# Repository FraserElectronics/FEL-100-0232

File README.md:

# FEL-100-0232
Z80 SoftROM Module PCB

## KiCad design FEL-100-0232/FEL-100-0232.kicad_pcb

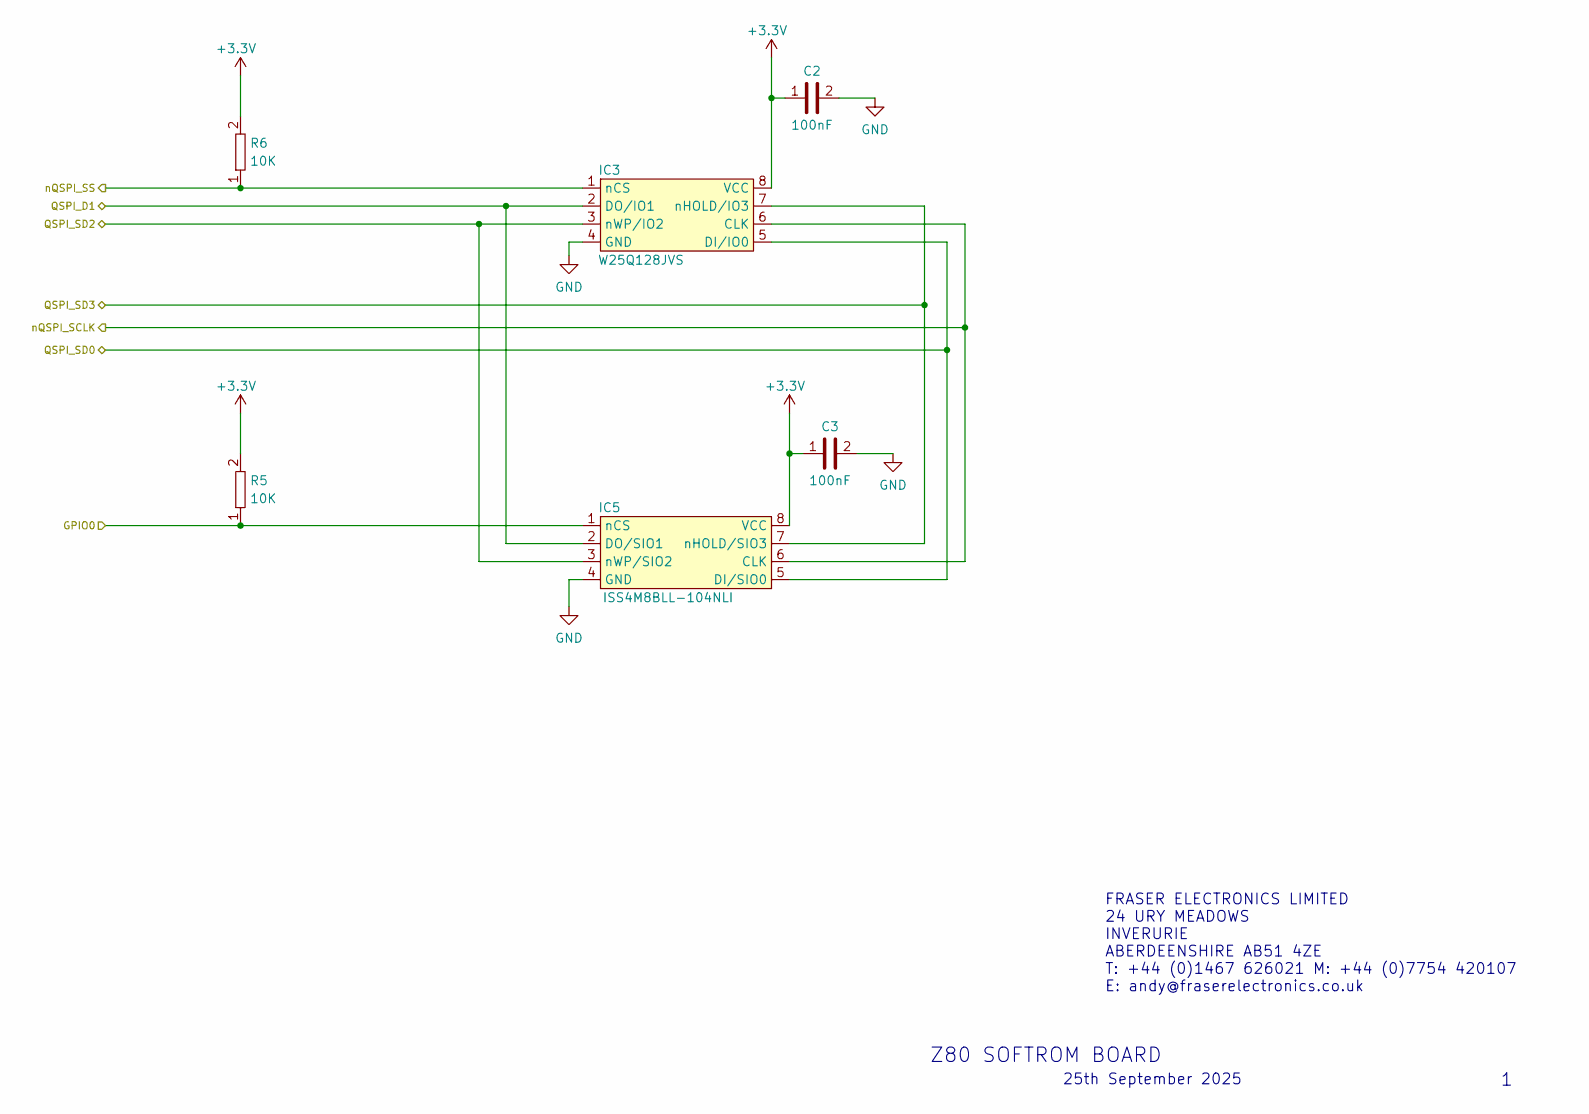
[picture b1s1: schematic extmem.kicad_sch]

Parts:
C2, C3: 100nF; C_0603_1608Metric; PartNumber FEL-002-0011
IC3: W25Q128JVS; SOIC-8_5.3x6.2mm_P1.27mm; PartNumber FEL-016-0290
IC5: ISS4M8BLL-104NLI; SOIC-8_5.3x6.2mm_P1.27mm; PartNumber FEL-016-0355
R5, R6: 10K; R_0603_1608Metric; PartNumber FEL-028-0028

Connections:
+3.3V: C2.1, C3.1, IC3.8 (VCC), IC5.8 (VCC), R5.2, R6.2; also elsewhere on the board
/External Memory/GPIO0: IC5.1 (nCS), R5.1; also elsewhere on the board
/External Memory/QSPI_D1: IC3.2 (DO/IO1), IC5.2 (DO/SIO1); also elsewhere on the board
/External Memory/QSPI_SD0: IC3.5 (DI/IO0), IC5.5 (DI/SIO0); also elsewhere on the board
/External Memory/QSPI_SD2: IC3.3 (nWP/IO2), IC5.3 (nWP/SIO2); also elsewhere on the board
/External Memory/QSPI_SD3: IC3.7 (nHOLD/IO3), IC5.7 (nHOLD/SIO3); also elsewhere on the board
/External Memory/nQSPI_SCLK: IC3.6 (CLK), IC5.6 (CLK); also elsewhere on the board
/RP2350B Micro/nQSPI_SS: IC3.1 (nCS), R6.1; also elsewhere on the board
GND: C2.2, C3.2, IC3.4 (GND), IC5.4 (GND); also elsewhere on the board

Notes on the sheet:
Z80 SOFTROM BOARD
FRASER ELECTRONICS LIMITED 24 URY MEADOWS INVERURIE ABERDEENSHIRE AB51 4ZE T: +44 (0)1467 626021 M: +44 (0)7754 420107 E: andy@fraserelectronics.co.uk
25th September 2025

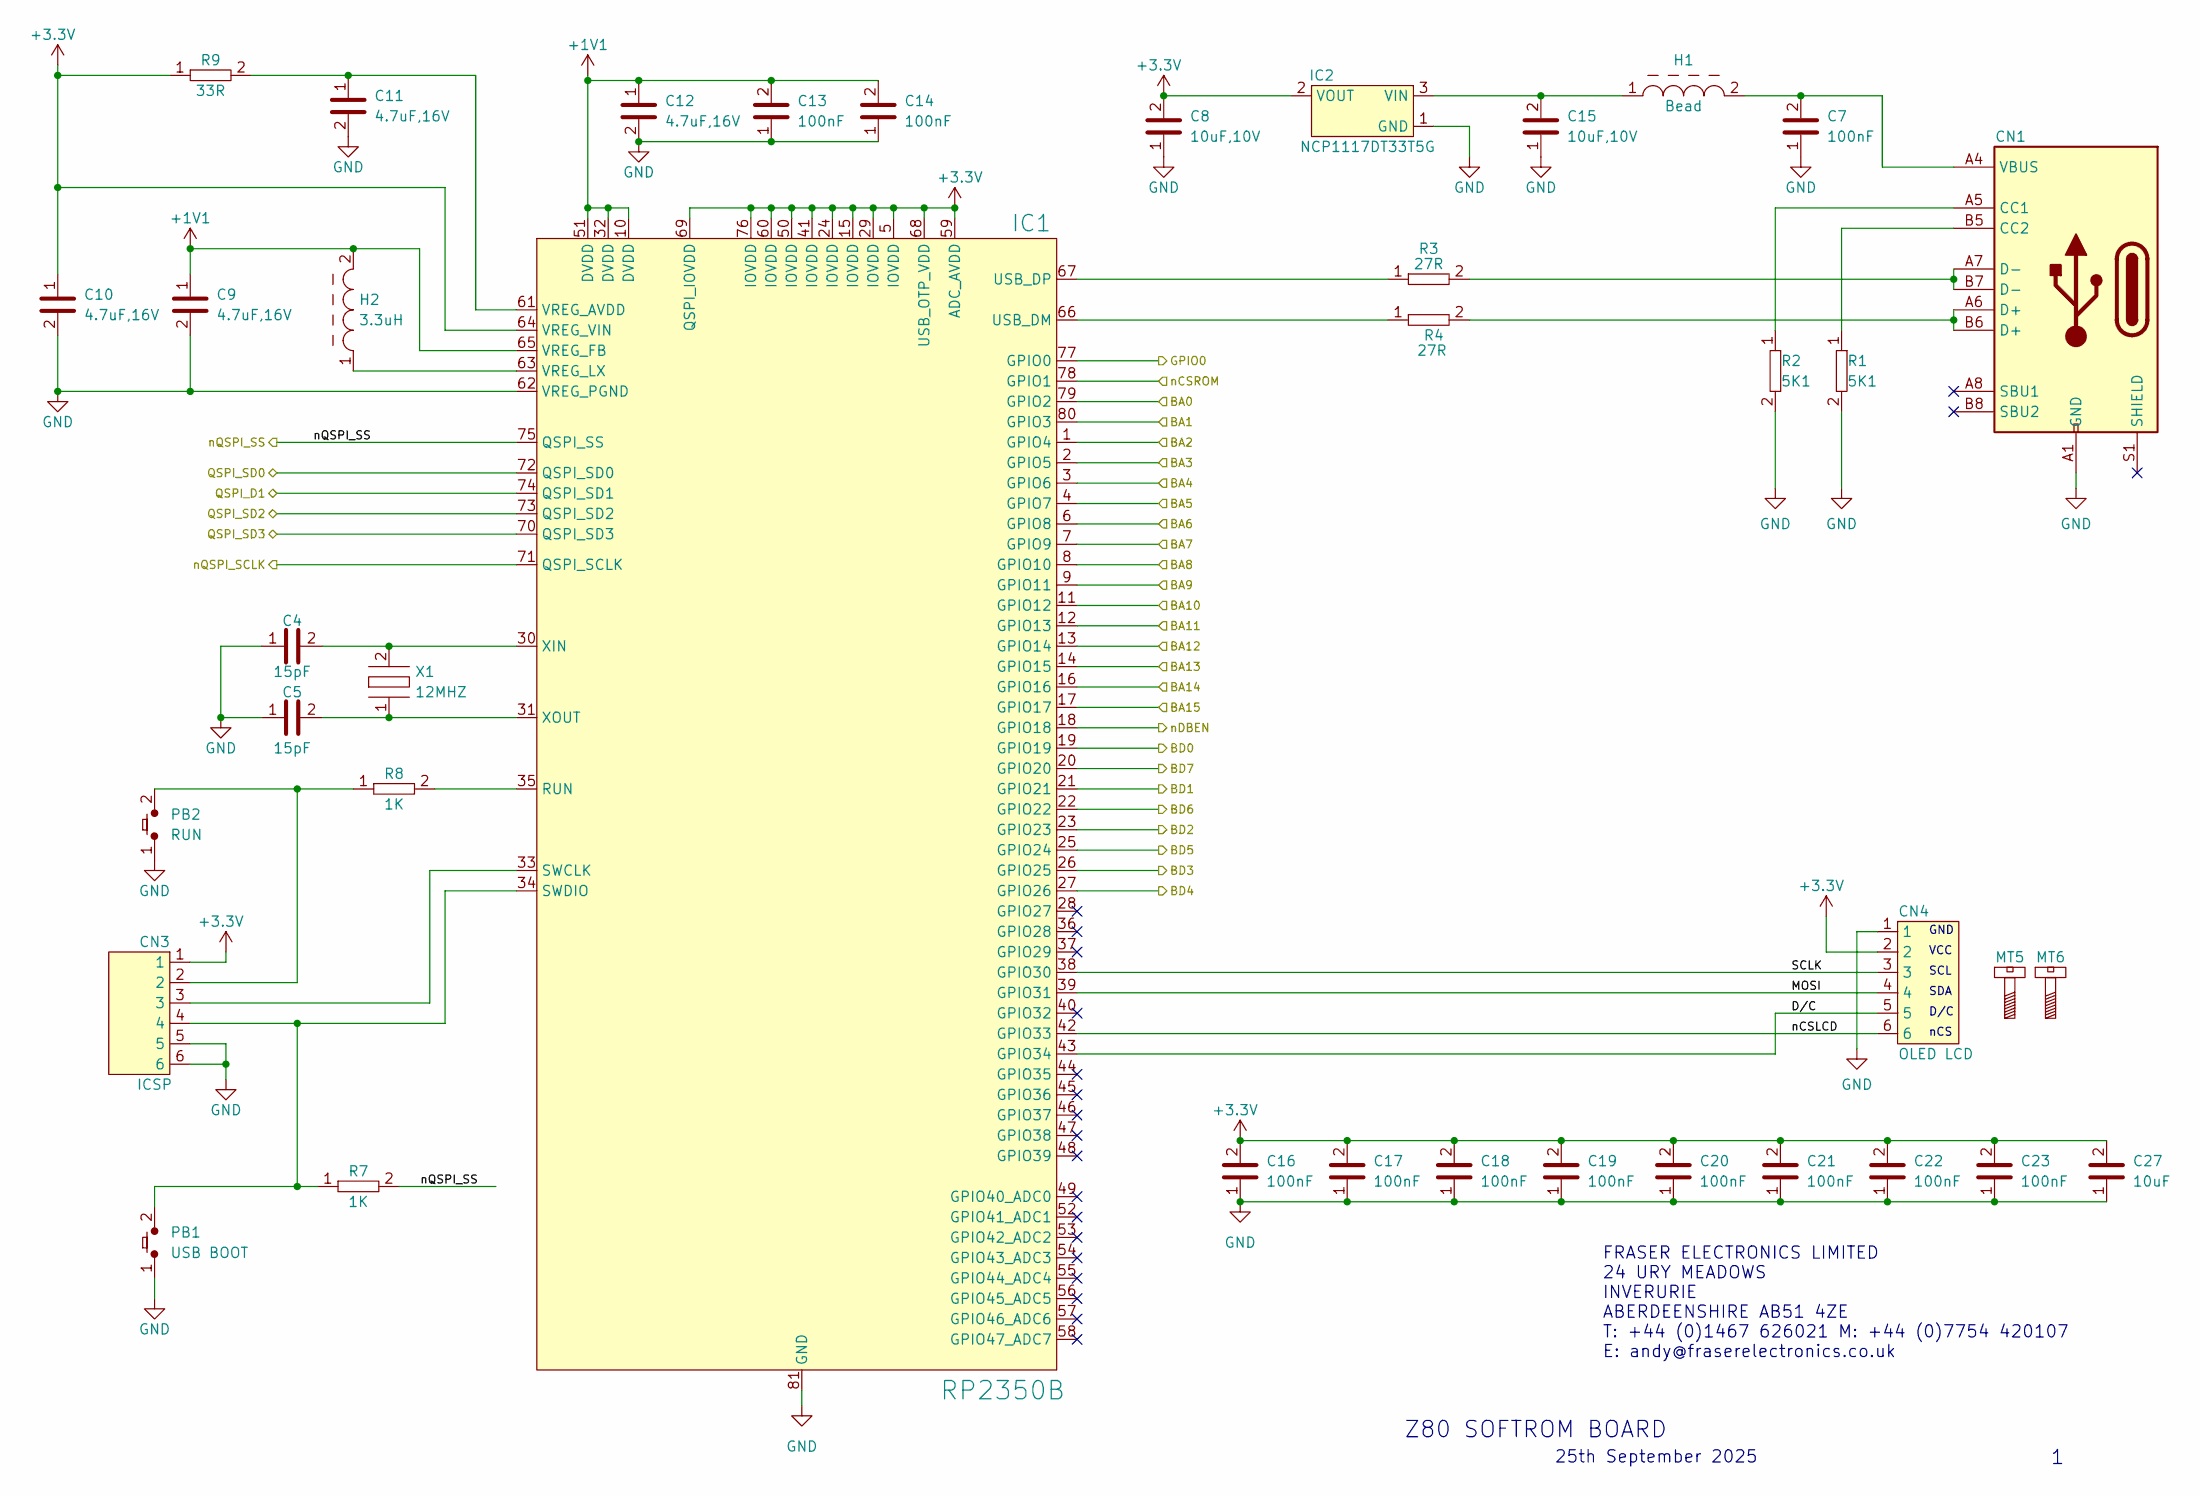
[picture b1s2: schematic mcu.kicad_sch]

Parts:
C4, C5: 15pF; C_0603_1608Metric; PartNumber FEL-002-0070
C7, C13, C14, C16, C17, C18, C19, C20, C21, C22, C23: 100nF; C_0603_1608Metric; PartNumber FEL-002-0011
C8, C15: 10uF,10V; C_0805_2012Metric; PartNumber FEL-002-0037
C9, C10, C11, C12: 4.7uF,16V; C_0805_2012Metric; PartNumber FEL-002-0013
C27: 10uF; C_0805_2012Metric; PartNumber FEL-002-0037
CN1: USB4105-GF-A-120; PartNumber FEL-004-0207
CN3: ICSP; M40-4010646R; PartNumber FEL-004-0006
CN4: OLED LCD; SIL6
H1: Bead; L_0603_1608Metric; PartNumber FEL-018-0016
H2: 3.3uH; AOTA-B201610S3R3-101-T; PartNumber FEL-018-0038
IC1: RP2350B; RP2350B_QFN-80_EP_10.573x10.573_Pitch0.4mm; PartNumber FEL-016-0353
IC2: NCP1117DT33T5G; TO-252-2; PartNumber FEL-016-0354
MT5, MT6: M3MountingHole
PB1: USB BOOT; EVQ-PT5A15; PartNumber FEL-030-0025
PB2: RUN; EVQ-PT5A15; PartNumber FEL-030-0025
R1, R2: 5K1; R_0603_1608Metric; PartNumber FEL-028-0083
R3, R4: 27R; R_0603_1608Metric; PartNumber FEL-028-0071
R7, R8: 1K; R_0603_1608Metric; PartNumber FEL-028-0037
R9: 33R; R_0603_1608Metric; PartNumber FEL-028-0045
X1: 12MHZ; ABM8-272-T3; PartNumber FEL-006-0008

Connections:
+1V1: C9.1, C12.1, C13.2, C14.2, H2.2, IC1.10 (DVDD), IC1.32 (DVDD), IC1.51 (DVDD), IC1.65 (VREG_FB)
+3.3V: C8.2, C10.1, C16.2, C17.2, C18.2, C19.2, C20.2, C21.2, C22.2, C23.2, C27.2, CN3.1, CN4.2, IC1.5 (IOVDD), IC1.15 (IOVDD), IC1.24 (IOVDD), IC1.29 (IOVDD), IC1.41 (IOVDD), IC1.50 (IOVDD), IC1.59 (ADC_AVDD), IC1.60 (IOVDD), IC1.64 (VREG_VIN), IC1.68 (USB_OTP_VDD), IC1.69 (QSPI_IOVDD), IC1.76 (IOVDD), IC2.2 (VOUT), R9.1; also elsewhere on the board
/External Memory/GPIO0: IC1.77 (GPIO0); also elsewhere on the board
/External Memory/QSPI_D1: IC1.74 (QSPI_SD1); also elsewhere on the board
/External Memory/QSPI_SD0: IC1.72 (QSPI_SD0); also elsewhere on the board
/External Memory/QSPI_SD2: IC1.73 (QSPI_SD2); also elsewhere on the board
/External Memory/QSPI_SD3: IC1.70 (QSPI_SD3); also elsewhere on the board
/External Memory/nQSPI_SCLK: IC1.71 (QSPI_SCLK); also elsewhere on the board
/RP2350B Micro/BA0: IC1.79 (GPIO2); also elsewhere on the board
/RP2350B Micro/BA1: IC1.80 (GPIO3); also elsewhere on the board
/RP2350B Micro/BA2: IC1.1 (GPIO4); also elsewhere on the board
/RP2350B Micro/BA3: IC1.2 (GPIO5); also elsewhere on the board
/RP2350B Micro/BA4: IC1.3 (GPIO6); also elsewhere on the board
/RP2350B Micro/BA5: IC1.4 (GPIO7); also elsewhere on the board
/RP2350B Micro/BA6: IC1.6 (GPIO8); also elsewhere on the board
/RP2350B Micro/BA7: IC1.7 (GPIO9); also elsewhere on the board
/RP2350B Micro/BA8: IC1.8 (GPIO10); also elsewhere on the board
/RP2350B Micro/BA9: IC1.9 (GPIO11); also elsewhere on the board
/RP2350B Micro/BA10: IC1.11 (GPIO12); also elsewhere on the board
/RP2350B Micro/BA11: IC1.12 (GPIO13); also elsewhere on the board
/RP2350B Micro/BA12: IC1.13 (GPIO14); also elsewhere on the board
/RP2350B Micro/BA13: IC1.14 (GPIO15); also elsewhere on the board
/RP2350B Micro/BA14: IC1.16 (GPIO16); also elsewhere on the board
/RP2350B Micro/BA15: IC1.17 (GPIO17); also elsewhere on the board
/RP2350B Micro/BD0: IC1.19 (GPIO19); also elsewhere on the board
/RP2350B Micro/BD1: IC1.21 (GPIO21); also elsewhere on the board
/RP2350B Micro/BD2: IC1.23 (GPIO23); also elsewhere on the board
/RP2350B Micro/BD3: IC1.26 (GPIO25); also elsewhere on the board
/RP2350B Micro/BD4: IC1.27 (GPIO26); also elsewhere on the board
/RP2350B Micro/BD5: IC1.25 (GPIO24); also elsewhere on the board
/RP2350B Micro/BD6: IC1.22 (GPIO22); also elsewhere on the board
/RP2350B Micro/BD7: IC1.20 (GPIO20); also elsewhere on the board
/RP2350B Micro/D/C: CN4.5, IC1.43 (GPIO34)
/RP2350B Micro/MOSI: CN4.4, IC1.39 (GPIO31)
/RP2350B Micro/SCLK: CN4.3, IC1.38 (GPIO30)
/RP2350B Micro/nCSLCD: CN4.6, IC1.42 (GPIO33)
/RP2350B Micro/nCSROM: IC1.78 (GPIO1); also elsewhere on the board
/RP2350B Micro/nQSPI_SS: IC1.75 (QSPI_SS), R7.2; also elsewhere on the board
/Z80 Interface/nDBEN: IC1.18 (GPIO18); also elsewhere on the board
GND: C4.1, C5.1, C7.1, C8.1, C9.2, C10.2, C11.2, C12.2, C13.1, C14.1, C15.1, C16.1, C17.1, C18.1, C19.1, C20.1, C21.1, C22.1, C23.1, C27.1, CN1.A1 (GND), CN1.A12 (GND), CN1.B1 (GND), CN1.B12 (GND), CN3.5, CN3.6, CN4.1, IC1.62 (VREG_PGND), IC1.81 (GND), IC2.1 (GND), PB1.1, PB2.1, R1.2, R2.2; also elsewhere on the board
unnamed: C7.2, CN1.A4 (VBUS), CN1.A9 (VBUS), CN1.B4 (VBUS), CN1.B9 (VBUS), H1.2
unnamed: CN1.A5 (CC1), R2.1
unnamed: CN1.B5 (CC2), R1.1
unnamed: CN1.A6 (D+), CN1.B6 (D+), R4.2
unnamed: CN1.A7 (D-), CN1.B7 (D-), R3.2
unnamed: CN3.2, PB2.2, R8.1
unnamed: IC1.35 (RUN), R8.2
unnamed: CN3.3, IC1.33 (SWCLK)
unnamed: CN3.4, IC1.34 (SWDIO), PB1.2, R7.1
unnamed: IC1.66 (USB_DM), R4.1
unnamed: IC1.67 (USB_DP), R3.1
unnamed: C11.1, IC1.61 (VREG_AVDD), R9.2
unnamed: H2.1, IC1.63 (VREG_LX)
unnamed: C4.2, IC1.30 (XIN), X1.2
unnamed: C5.2, IC1.31 (XOUT), X1.1
unnamed: C15.2, H1.1, IC2.3 (VIN)

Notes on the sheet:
GND
SDA
FRASER ELECTRONICS LIMITED 24 URY MEADOWS INVERURIE ABERDEENSHIRE AB51 4ZE T: +44 (0)1467 626021 M: +44 (0)7754 420107 E: andy@fraserelectronics.co.uk
SCL
Z80 SOFTROM BOARD
nCS
VCC
D/C
25th September 2025

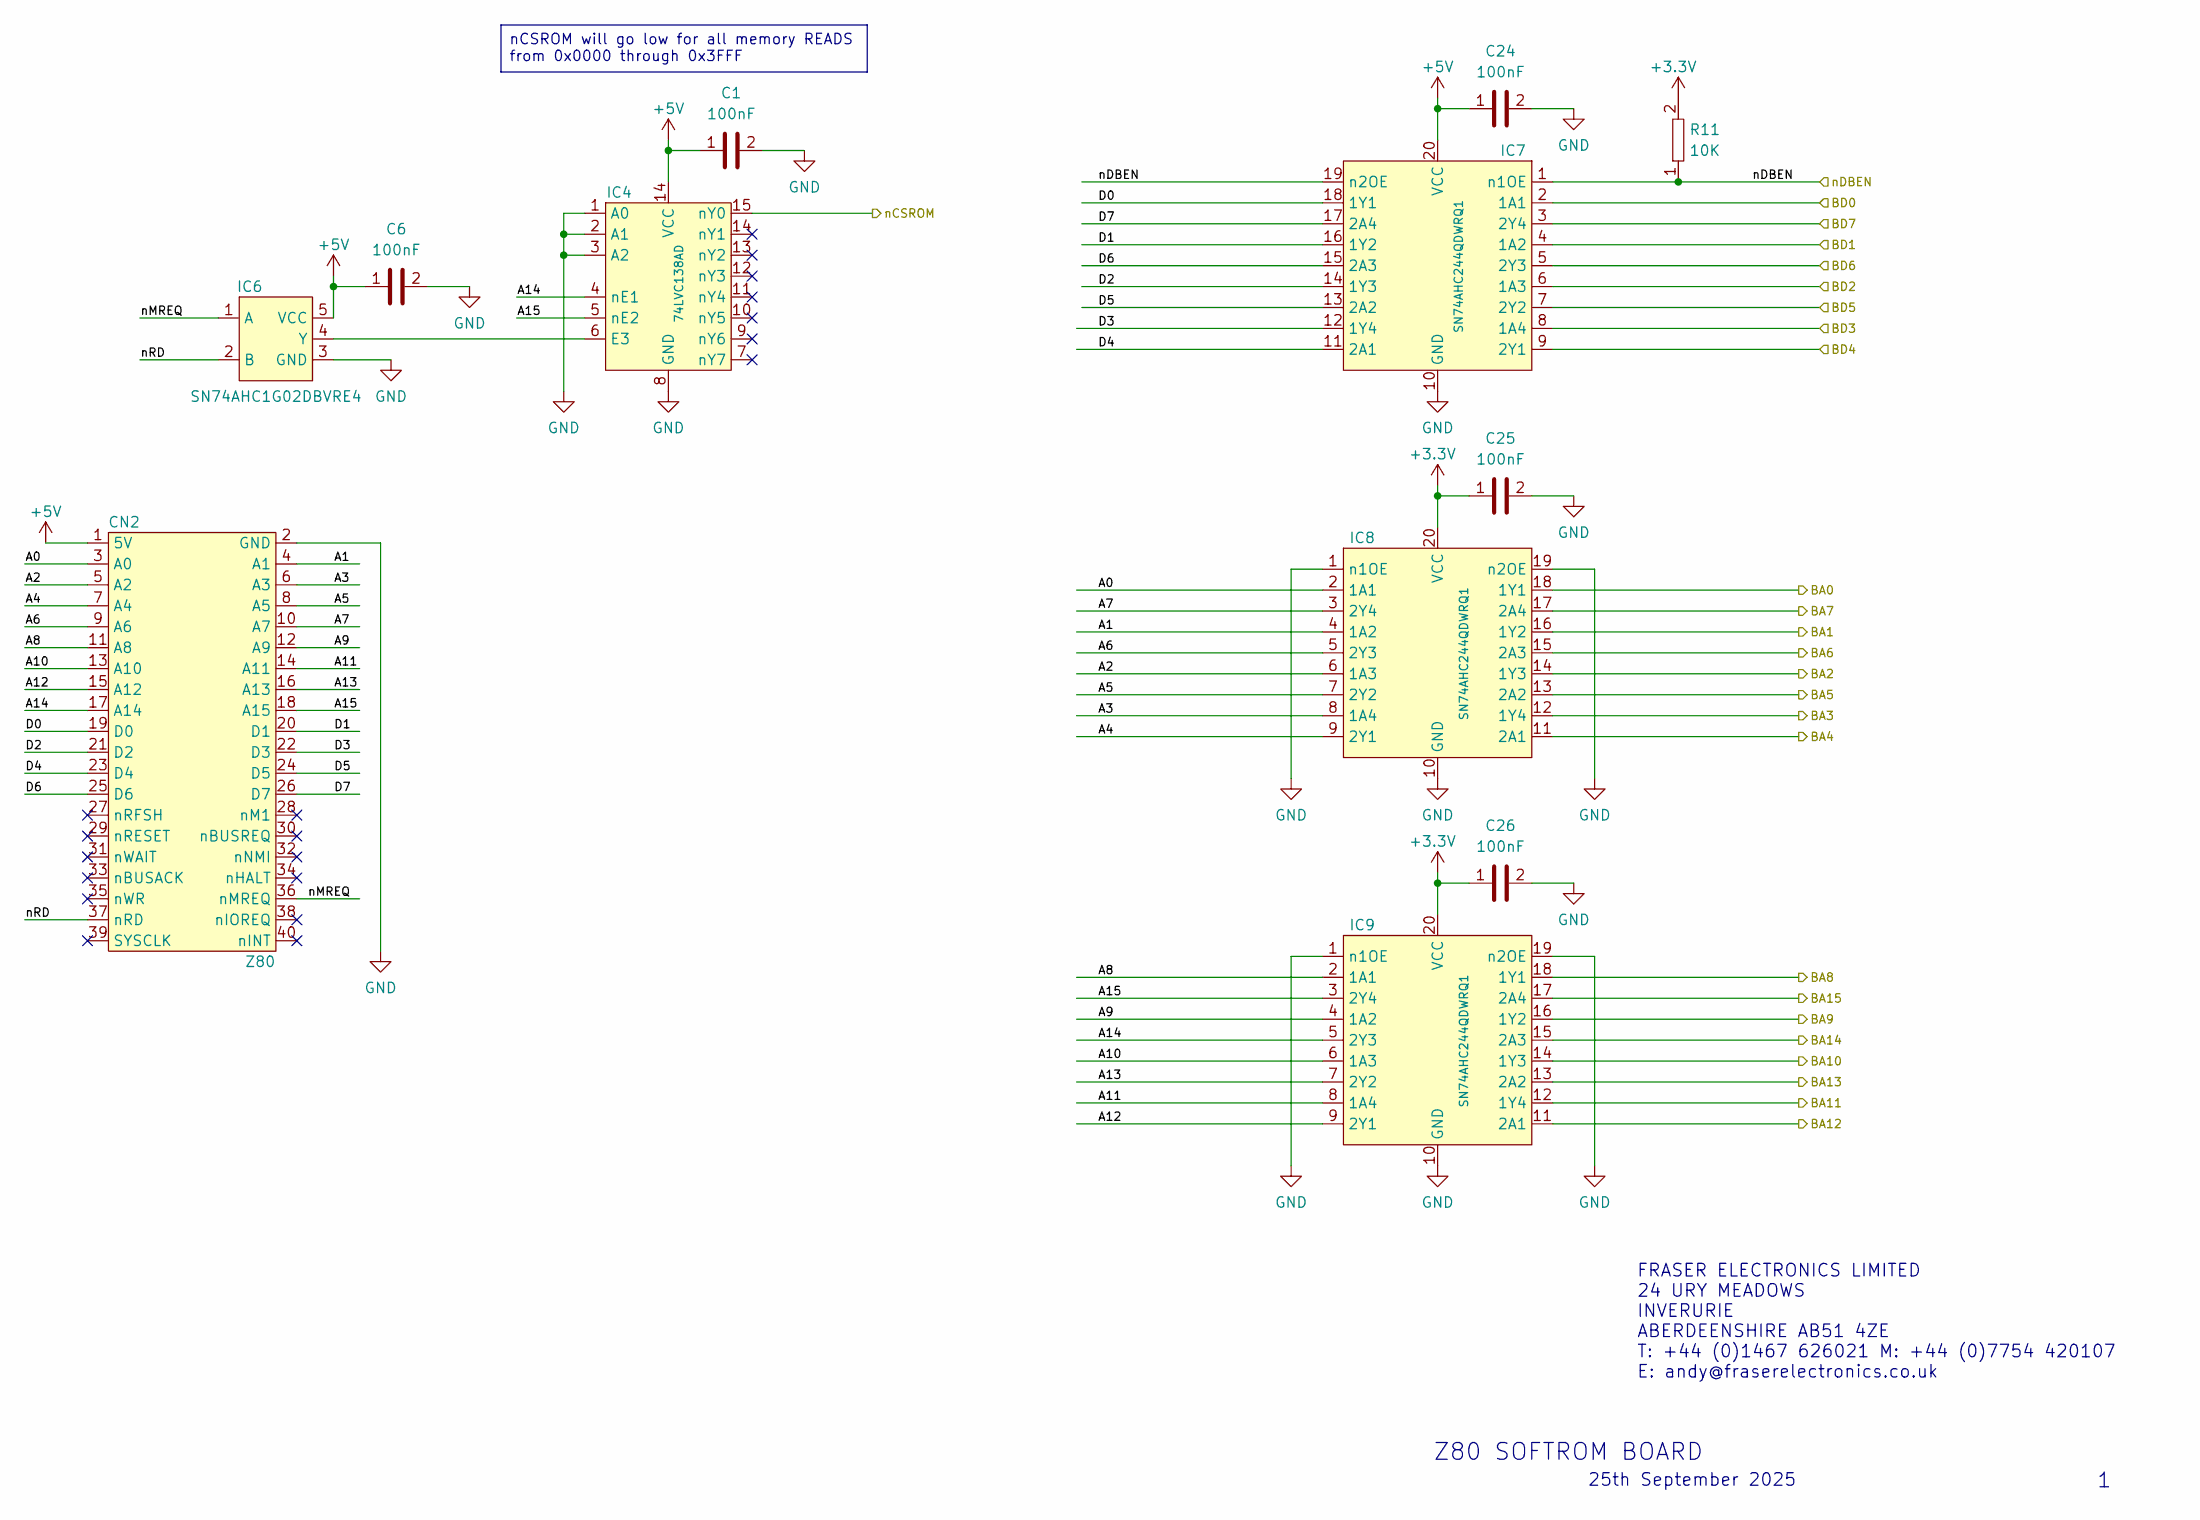
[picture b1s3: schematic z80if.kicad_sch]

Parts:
C1, C6, C24, C25, C26: 100nF; C_0603_1608Metric; PartNumber FEL-002-0011
CN2: Z80; Z80CONNECTOR
IC4: 74LVC138AD; SOIC-16W_5.3x10.2mm_P1.27mm; PartNumber FEL-016-0335
IC6: SN74AHC1G02DBVRE4; SOT-23-5_HandSoldering; PartNumber FEL-016-0357
IC7, IC8, IC9: SN74AHC244QDWRQ1; SOIC-20W_7.5x12.8mm_P1.27mm; PartNumber FEL-016-0356
R11: 10K; R_0603_1608Metric; PartNumber FEL-028-0028

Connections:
+3.3V: C25.1, C26.1, IC8.20 (VCC), IC9.20 (VCC), R11.2; also elsewhere on the board
+5V: C1.1, C6.1, C24.1, CN2.1 (5V), IC4.14 (VCC), IC6.5 (VCC), IC7.20 (VCC)
/RP2350B Micro/BA0: IC8.18 (1Y1); also elsewhere on the board
/RP2350B Micro/BA1: IC8.16 (1Y2); also elsewhere on the board
/RP2350B Micro/BA2: IC8.14 (1Y3); also elsewhere on the board
/RP2350B Micro/BA3: IC8.12 (1Y4); also elsewhere on the board
/RP2350B Micro/BA4: IC8.11 (2A1); also elsewhere on the board
/RP2350B Micro/BA5: IC8.13 (2A2); also elsewhere on the board
/RP2350B Micro/BA6: IC8.15 (2A3); also elsewhere on the board
/RP2350B Micro/BA7: IC8.17 (2A4); also elsewhere on the board
/RP2350B Micro/BA8: IC9.18 (1Y1); also elsewhere on the board
/RP2350B Micro/BA9: IC9.16 (1Y2); also elsewhere on the board
/RP2350B Micro/BA10: IC9.14 (1Y3); also elsewhere on the board
/RP2350B Micro/BA11: IC9.12 (1Y4); also elsewhere on the board
/RP2350B Micro/BA12: IC9.11 (2A1); also elsewhere on the board
/RP2350B Micro/BA13: IC9.13 (2A2); also elsewhere on the board
/RP2350B Micro/BA14: IC9.15 (2A3); also elsewhere on the board
/RP2350B Micro/BA15: IC9.17 (2A4); also elsewhere on the board
/RP2350B Micro/BD0: IC7.2 (1A1); also elsewhere on the board
/RP2350B Micro/BD1: IC7.4 (1A2); also elsewhere on the board
/RP2350B Micro/BD2: IC7.6 (1A3); also elsewhere on the board
/RP2350B Micro/BD3: IC7.8 (1A4); also elsewhere on the board
/RP2350B Micro/BD4: IC7.9 (2Y1); also elsewhere on the board
/RP2350B Micro/BD5: IC7.7 (2Y2); also elsewhere on the board
/RP2350B Micro/BD6: IC7.5 (2Y3); also elsewhere on the board
/RP2350B Micro/BD7: IC7.3 (2Y4); also elsewhere on the board
/RP2350B Micro/nCSROM: IC4.15 (nY0); also elsewhere on the board
/Z80 Interface/A0: CN2.3 (A0), IC8.2 (1A1)
/Z80 Interface/A1: CN2.4 (A1), IC8.4 (1A2)
/Z80 Interface/A2: CN2.5 (A2), IC8.6 (1A3)
/Z80 Interface/A3: CN2.6 (A3), IC8.8 (1A4)
/Z80 Interface/A4: CN2.7 (A4), IC8.9 (2Y1)
/Z80 Interface/A5: CN2.8 (A5), IC8.7 (2Y2)
/Z80 Interface/A6: CN2.9 (A6), IC8.5 (2Y3)
/Z80 Interface/A7: CN2.10 (A7), IC8.3 (2Y4)
/Z80 Interface/A8: CN2.11 (A8), IC9.2 (1A1)
/Z80 Interface/A9: CN2.12 (A9), IC9.4 (1A2)
/Z80 Interface/A10: CN2.13 (A10), IC9.6 (1A3)
/Z80 Interface/A11: CN2.14 (A11), IC9.8 (1A4)
/Z80 Interface/A12: CN2.15 (A12), IC9.9 (2Y1)
/Z80 Interface/A13: CN2.16 (A13), IC9.7 (2Y2)
/Z80 Interface/A14: CN2.17 (A14), IC4.4 (nE1), IC9.5 (2Y3)
/Z80 Interface/A15: CN2.18 (A15), IC4.5 (nE2), IC9.3 (2Y4)
/Z80 Interface/D0: CN2.19 (D0), IC7.18 (1Y1)
/Z80 Interface/D1: CN2.20 (D1), IC7.16 (1Y2)
/Z80 Interface/D2: CN2.21 (D2), IC7.14 (1Y3)
/Z80 Interface/D3: CN2.22 (D3), IC7.12 (1Y4)
/Z80 Interface/D4: CN2.23 (D4), IC7.11 (2A1)
/Z80 Interface/D5: CN2.24 (D5), IC7.13 (2A2)
/Z80 Interface/D6: CN2.25 (D6), IC7.15 (2A3)
/Z80 Interface/D7: CN2.26 (D7), IC7.17 (2A4)
/Z80 Interface/nDBEN: IC7.1 (n1OE), IC7.19 (n2OE), R11.1; also elsewhere on the board
/Z80 Interface/nMREQ: CN2.36 (nMREQ), IC6.1 (A)
/Z80 Interface/nRD: CN2.37 (nRD), IC6.2 (B)
GND: C1.2, C6.2, C24.2, C25.2, C26.2, CN2.2 (GND), IC4.1 (A0), IC4.2 (A1), IC4.3 (A2), IC4.8 (GND), IC6.3 (GND), IC7.10 (GND), IC8.1 (n1OE), IC8.10 (GND), IC8.19 (n2OE), IC9.1 (n1OE), IC9.10 (GND), IC9.19 (n2OE); also elsewhere on the board
unnamed: IC4.6 (E3), IC6.4 (Y)

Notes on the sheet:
Z80 SOFTROM BOARD
25th September 2025
FRASER ELECTRONICS LIMITED 24 URY MEADOWS INVERURIE ABERDEENSHIRE AB51 4ZE T: +44 (0)1467 626021 M: +44 (0)7754 420107 E: andy@fraserelectronics.co.uk
nCSROM will go low for all memory READS from 0x0000 through 0x3FFF

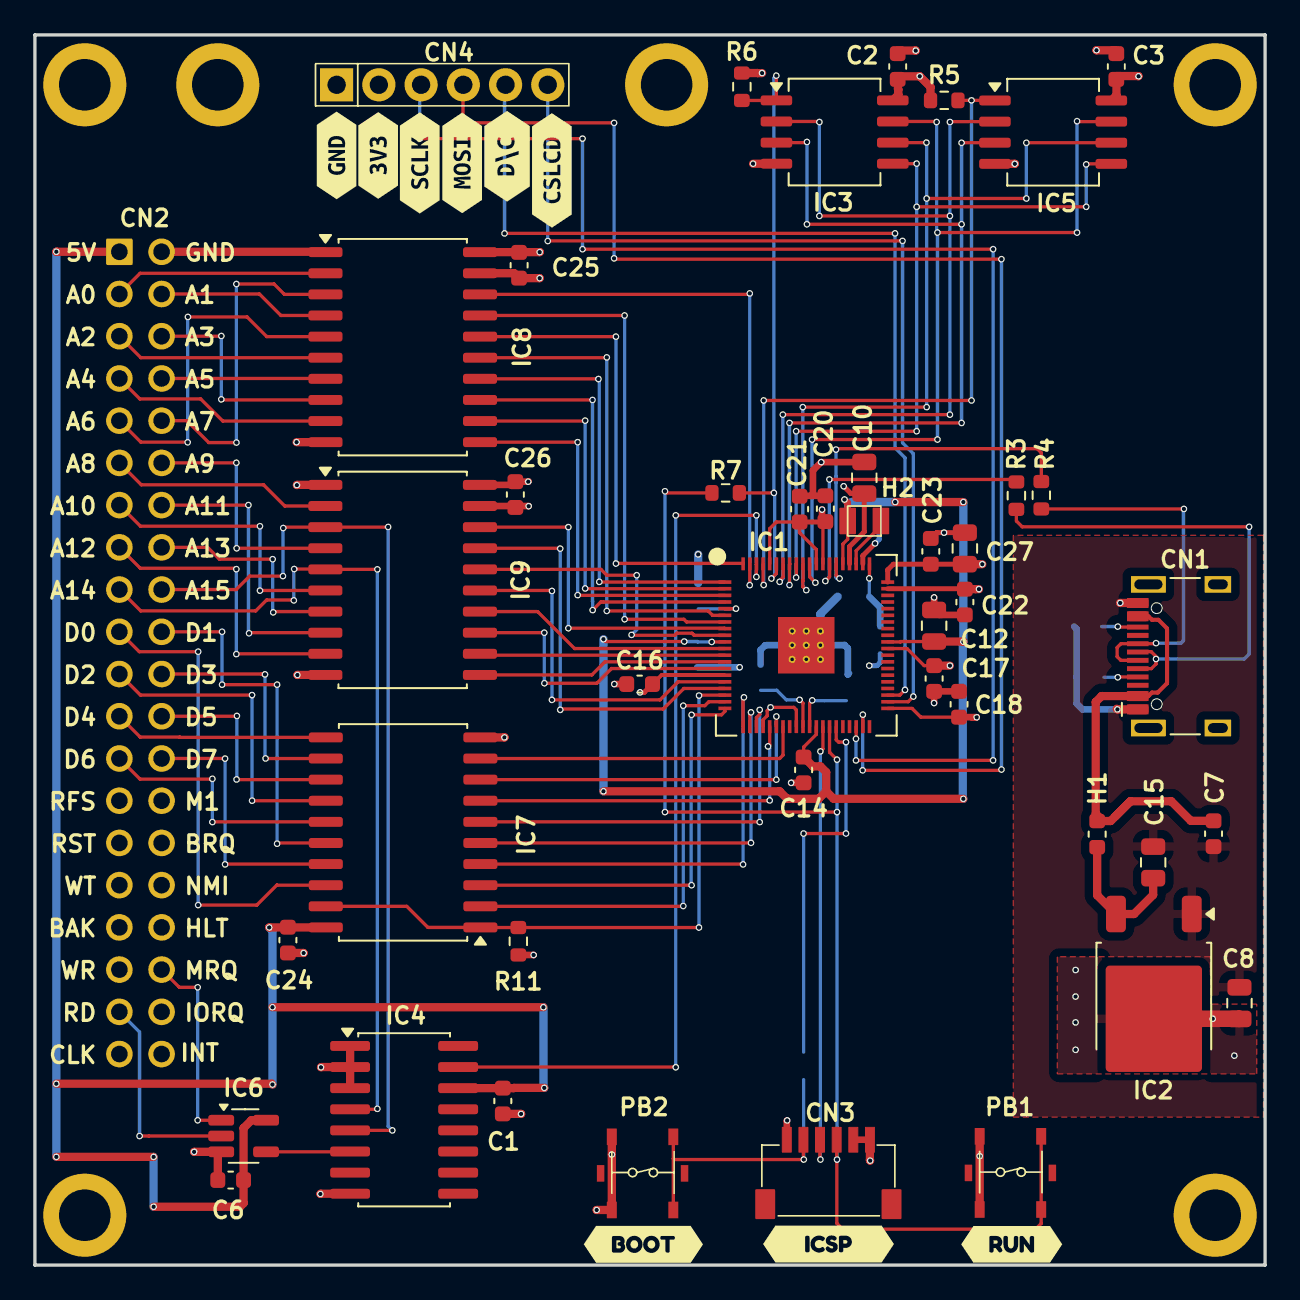
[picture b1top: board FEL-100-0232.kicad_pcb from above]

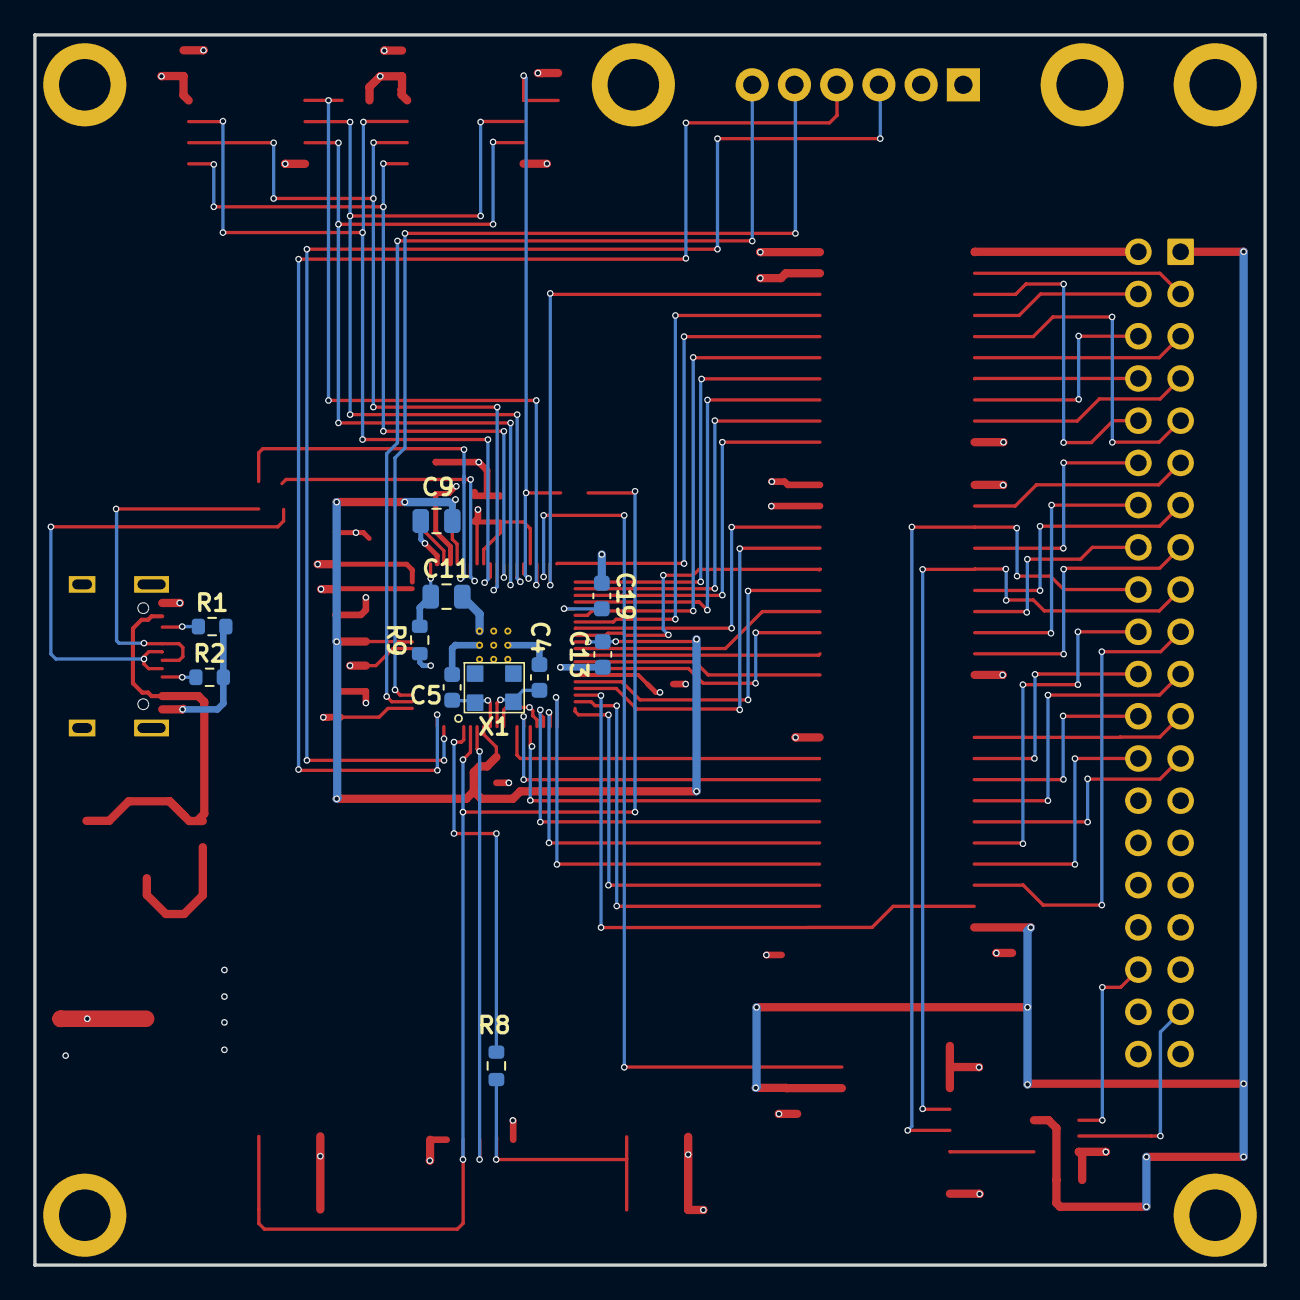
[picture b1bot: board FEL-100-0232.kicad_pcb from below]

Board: 4 copper layers, 74.0 x 74.0 mm, 70 parts (11 on the bottom side), 84 nets.

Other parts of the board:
MT1, MT2, MT3, MT4: M3MountingHole
kibuzzard-68E53301: G***; kibuzzard-68E53301
kibuzzard-68E53357: G***; kibuzzard-68E53357
kibuzzard-68E53383: G***; kibuzzard-68E53383
kibuzzard-68F144A5: G***; kibuzzard-68F144A5
kibuzzard-68F144C2: G***; kibuzzard-68F144C2
kibuzzard-68F144D2: G***; kibuzzard-68F144D2
kibuzzard-68F1446B: G***; kibuzzard-68F1446B
kibuzzard-68F1449B: G***; kibuzzard-68F1449B
kibuzzard-68F14479: G***; kibuzzard-68F14479

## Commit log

2025-11-21 Work in progress.
